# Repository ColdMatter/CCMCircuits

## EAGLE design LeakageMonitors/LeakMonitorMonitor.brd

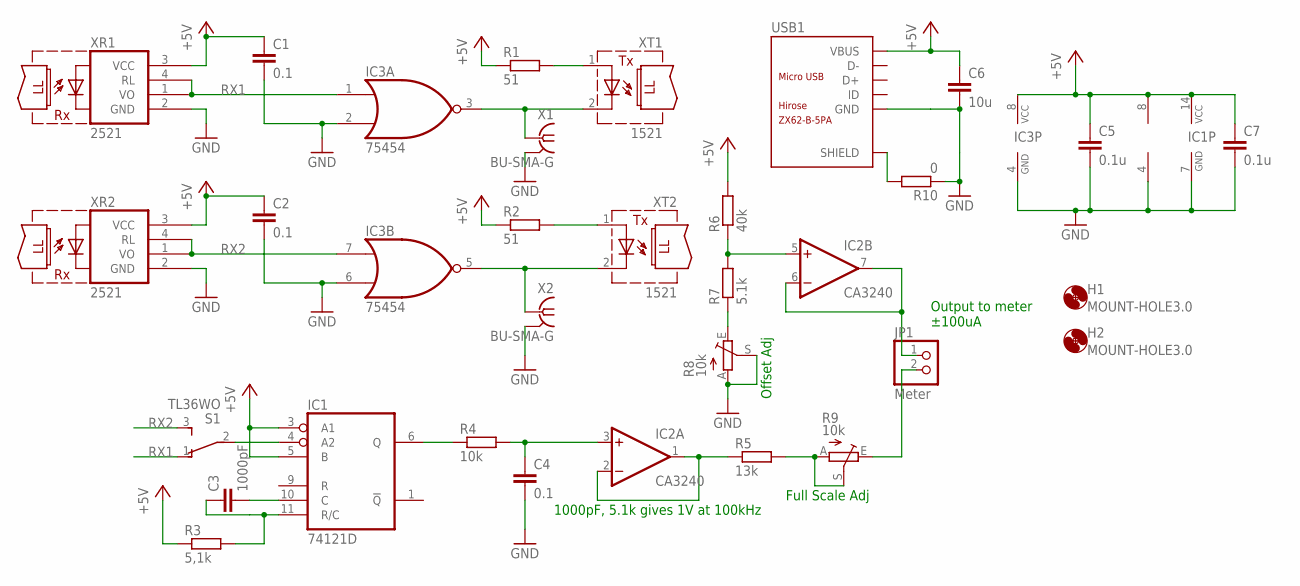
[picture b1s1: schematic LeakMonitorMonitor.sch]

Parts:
C1, C2, C4: 0.1; C0805
C3: 1000pF; C0805
C5, C7: 0.1u; C0805
C6: 10u; C1206
H1, H2: MOUNT-HOLE3.0; 3,0
IC1: 74121D; SO14
IC2: CA3240; SO08
IC3: 75454; D_R-PDSO-G8
JP1: Meter; 1X02
R1, R2: 51; M0805
R3: 5,1k; M0805
R4: 10k; M0805
R5: 13k; M0805
R6: 40k; M0805
R7: 5.1k; M0805
R8, R9: 10k; B25X
R10: 0; R0805
S1: TL36WO; TL3XWO
USB1: ZX62-B-5PA; MICRO-USB5+6P-SMD-0.65-AB
X1, X2: BU-SMA-G
XR1, XR2: 2521; HFBR-15X3
XT1, XT2: 1521; HFBR-15X3

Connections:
+5V: C1.1, C2.1, C5.1, C6.1, C7.1, IC1.3 (A1), IC1.5 (B), IC1.14 (VCC), IC2.8 (V+), IC3.8 (VCC), R1.1, R2.1, R3.1, R6.2, USB1.1 (VBUS), XR1.3 (VCC), XR2.3 (VCC)
GND: C1.2, C2.2, C4.2, C5.2, C6.2, C7.2, IC1.7 (GND), IC2.4 (V-), IC3.2 (I1), IC3.4 (GND), IC3.6 (I1), R8.A, R8.S, R10.1, USB1.5 (GND), X1.2, X1.3 (2), X1.4 (2), X1.5 (2), X2.2, X2.3 (2), X2.4 (2), X2.5 (2), XR1.2 (GND), XR2.2 (GND)
unnamed: IC3.3 (O), X1.1, XT1.2 (C)
unnamed: IC2.5 (+IN), R6.1, R7.2
unnamed: R7.1, R8.E
unnamed: IC3.5 (O), X2.1, XT2.2 (C)
unnamed: R2.2, XT2.1 (A)
unnamed: R1.2, XT1.1 (A)
unnamed: C3.2, IC1.10 (C)
unnamed: IC2.1 (OUT), IC2.2 (-IN), R5.1
unnamed: R5.2, R9.A, R9.S
unnamed: JP1.2, R9.E
unnamed: IC2.6 (-IN), IC2.7 (OUT), JP1.1
unnamed: C3.1, IC1.11 (R/C), R3.2
unnamed: IC1.6 (Q), R4.1
unnamed: C4.1, IC2.3 (+IN), R4.2
unnamed: IC1.4 (A2), S1.2
RX1: IC3.1 (I0), S1.1 (O), XR1.1 (VO), XR1.4 (RL)
RX2: IC3.7 (I0), S1.3 (S), XR2.1 (VO), XR2.4 (RL)
SHIELD: R10.2, USB1.P1 (SHIELD), USB1.P2 (SHIELD), USB1.P3 (SHIELD), USB1.P4 (SHIELD), USB1.P5 (SHIELD), USB1.P6 (SHIELD)

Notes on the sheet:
Output to meter ±100uA
Offset Adj
Full Scale Adj
1000pF, 5.1k gives 1V at 100kHz

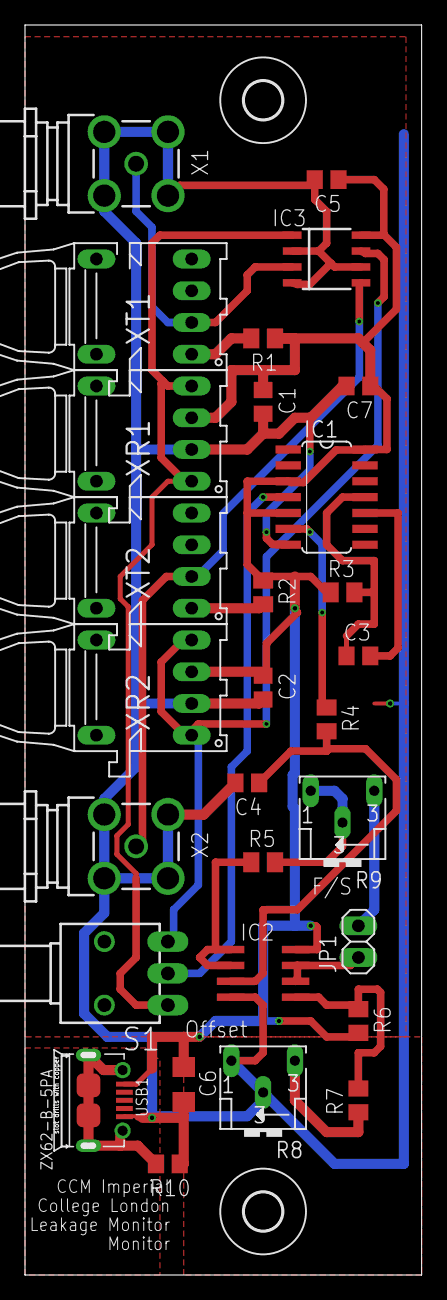
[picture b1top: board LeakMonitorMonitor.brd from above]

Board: 2 copper layers, 31.7 x 100.0 mm, 31 parts (0 on the bottom side), 20 nets.

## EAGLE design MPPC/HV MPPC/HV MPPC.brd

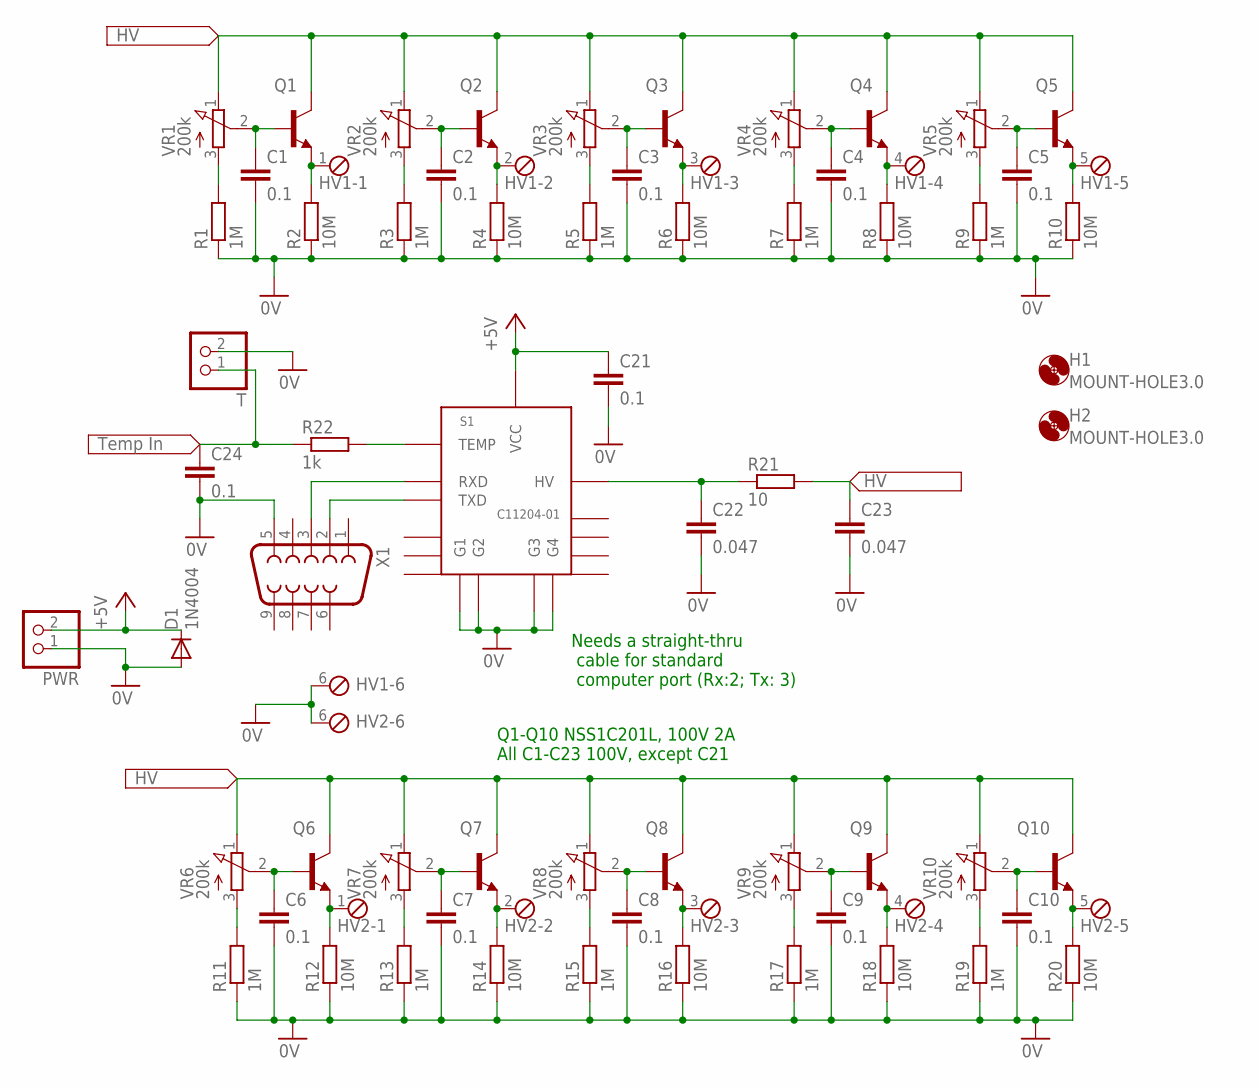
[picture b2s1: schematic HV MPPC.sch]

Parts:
C1, C2, C3, C4, C5, C6, C7, C8, C9, C10, C21, C24: 0.1; C0805
C22, C23: 0.047; C0805
D1: 1N4004; DO41-10
H1, H2: MOUNT-HOLE3.0; 3,0
HV1, HV2: MPT6; 6POL254
PWR: PINHD-1X2; 1X02
Q1, Q2, Q3, Q4, Q5, Q6, Q7, Q8, Q9, Q10: NSS1C201L; SOT23
R1, R3, R5, R7, R9, R11, R13, R15, R17, R19: 1M; R0805
R2, R4, R6, R8, R10, R12, R14, R16, R18, R20: 10M; R0805
R21: 10; R0805
R22: 1k; R0805
S1: C11204-01
T: PINHD-1X2; 1X02
VR1, VR2, VR3, VR4, VR5, VR6, VR7, VR8, VR9, VR10: 200k; 3314G
X1: F09HP

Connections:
0V: C1.2, C2.2, C3.2, C4.2, C5.2, C6.2, C7.2, C8.2, C9.2, C10.2, C21.2, C22.2, C23.2, C24.2, D1.A, HV1.6, HV2.6, PWR.1, R1.1, R2.1, R3.1, R4.1, R5.1, R6.1, R7.1, R8.1, R9.1, R10.1, R11.1, R12.1, R13.1, R14.1, R15.1, R16.1, R17.1, R18.1, R19.1, R20.1, S1.P$2 (G1), S1.P$5 (G2), S1.P$8 (G3), S1.P$15 (G4), T.2, X1.5
+5V: C21.1, D1.C, PWR.2, S1.P$1 (VCC)
HV: C22.1, R21.1, S1.P$10 (HV)
HVOUT: C23.1, Q1.3 (C), Q2.3 (C), Q3.3 (C), Q4.3 (C), Q5.3 (C), Q6.3 (C), Q7.3 (C), Q8.3 (C), Q9.3 (C), Q10.3 (C), R21.2, VR1.1 (E), VR2.1 (E), VR3.1 (E), VR4.1 (E), VR5.1 (E), VR6.1 (E), VR7.1 (E), VR8.1 (E), VR9.1 (E), VR10.1 (E)
unnamed: C1.1, Q1.1 (B), VR1.2 (S)
unnamed: C24.1, R22.1, T.1
unnamed: R22.2, S1.P$16 (TEMP)
unnamed: R1.2, VR1.3 (A)
unnamed: HV1.1, Q1.2 (E), R2.2
unnamed: R3.2, VR2.3 (A)
unnamed: HV1.2, Q2.2 (E), R4.2
unnamed: R5.2, VR3.3 (A)
unnamed: HV1.3, Q3.2 (E), R6.2
unnamed: R7.2, VR4.3 (A)
unnamed: HV1.4, Q4.2 (E), R8.2
unnamed: R9.2, VR5.3 (A)
unnamed: HV1.5, Q5.2 (E), R10.2
unnamed: C2.1, Q2.1 (B), VR2.2 (S)
unnamed: C3.1, Q3.1 (B), VR3.2 (S)
unnamed: C4.1, Q4.1 (B), VR4.2 (S)
unnamed: C5.1, Q5.1 (B), VR5.2 (S)
unnamed: C6.1, Q6.1 (B), VR6.2 (S)
unnamed: C7.1, Q7.1 (B), VR7.2 (S)
unnamed: C8.1, Q8.1 (B), VR8.2 (S)
unnamed: C9.1, Q9.1 (B), VR9.2 (S)
unnamed: C10.1, Q10.1 (B), VR10.2 (S)
unnamed: R11.2, VR6.3 (A)
unnamed: HV2.1, Q6.2 (E), R12.2
unnamed: R13.2, VR7.3 (A)
unnamed: HV2.2, Q7.2 (E), R14.2
unnamed: R15.2, VR8.3 (A)
unnamed: HV2.3, Q8.2 (E), R16.2
unnamed: R17.2, VR9.3 (A)
unnamed: R19.2, VR10.3 (A)
unnamed: HV2.5, Q10.2 (E), R20.2
unnamed: HV2.4, Q9.2 (E), R18.2
RX: S1.P$3 (RXD), X1.3
TX: S1.P$4 (TXD), X1.2

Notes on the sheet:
Q1-Q10 NSS1C201L, 100V 2A All C1-C23 100V, except C21
Needs a straight-thru cable for standard computer port (Rx:2; Tx: 3)

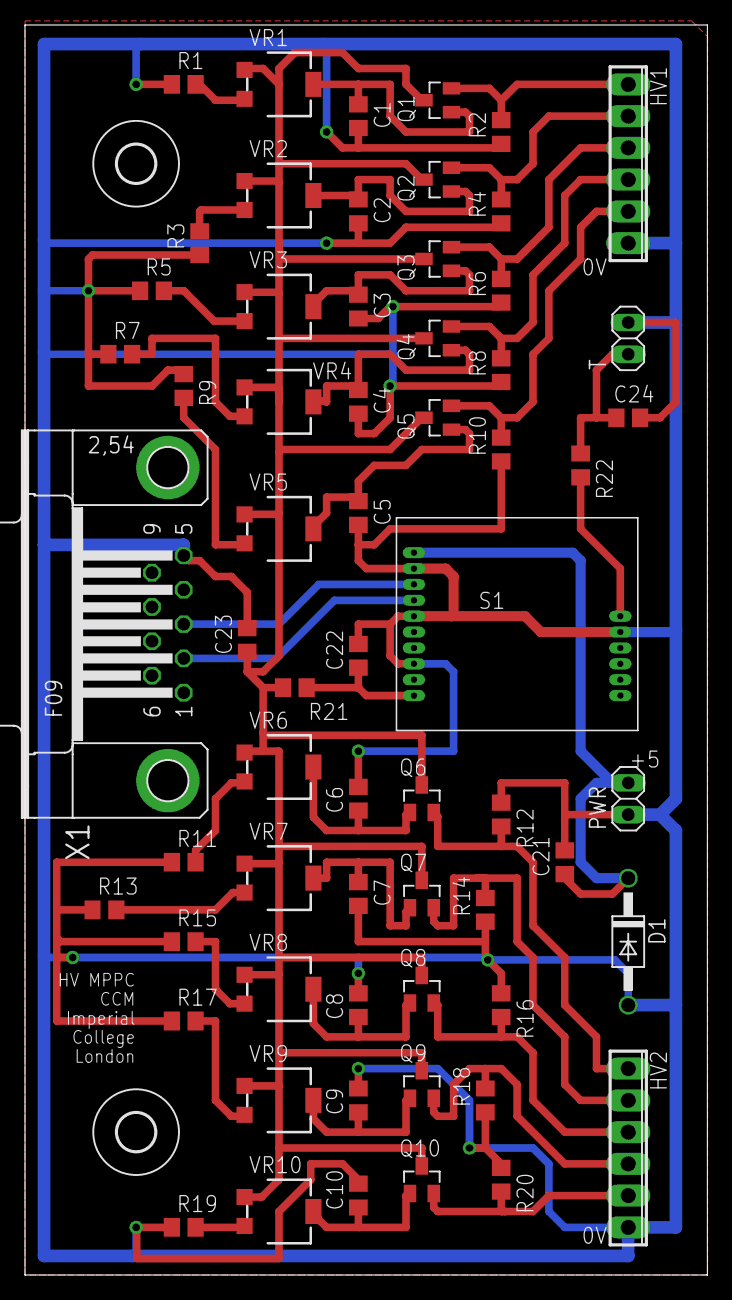
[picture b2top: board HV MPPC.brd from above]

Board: 2 copper layers, 54.6 x 100.0 mm, 65 parts (0 on the bottom side), 38 nets.

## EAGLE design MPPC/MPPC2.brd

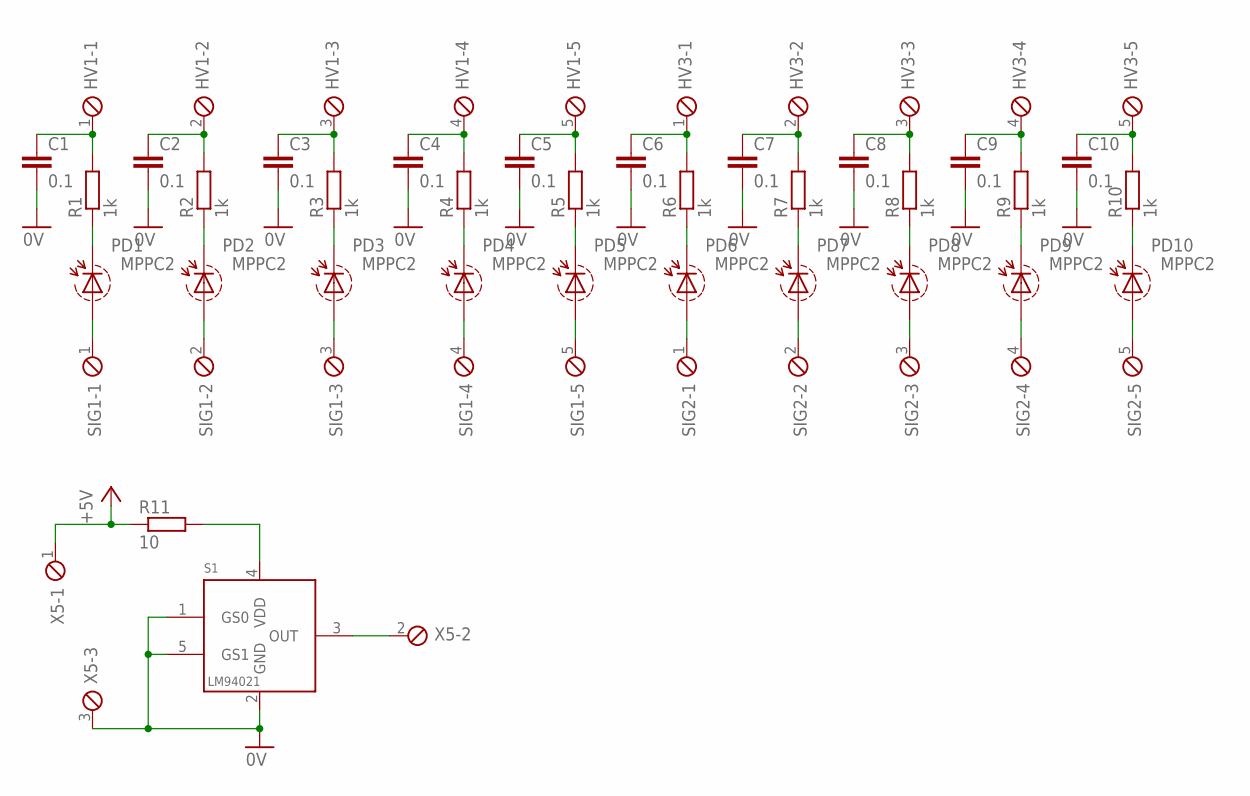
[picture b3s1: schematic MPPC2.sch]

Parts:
C1, C2, C3, C4, C5, C6, C7, C8, C9, C10: 0.1; C0805K
HV1, HV3: MPT5; 5POL254
PD1, PD2, PD3, PD4, PD5, PD6, PD7, PD8, PD9, PD10: MPPC2; S13360-6050VE
R1, R2, R3, R4, R5, R6, R7, R8, R9, R10: 1k; M0805
R11: 10; R0805
S1: LM94021; DCK_R-PDSO-G5
SIG1, SIG2: MPT5; 5POL254
X5: MPT3; 3POL254

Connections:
0V: C1.2, C2.2, C3.2, C4.2, C5.2, C6.2, C7.2, C8.2, C9.2, C10.2, S1.1 (GS0), S1.2 (GND), S1.5 (GS1), X5.3
+5V: R11.1, X5.1
unnamed: PD2.C1 (CATH), PD2.C2 (CATH), PD2.C3 (CATH), PD2.C4 (CATH), R2.1
unnamed: R11.2, S1.4 (VDD)
unnamed: S1.3 (OUT), X5.2
unnamed: C1.1, HV1.1, R1.2
unnamed: PD1.C1 (CATH), PD1.C2 (CATH), PD1.C3 (CATH), PD1.C4 (CATH), R1.1
unnamed: PD1.A1 (ANODE), PD1.A2 (ANODE), PD1.A3 (ANODE), PD1.A4 (ANODE), SIG1.1
unnamed: PD2.A1 (ANODE), PD2.A2 (ANODE), PD2.A3 (ANODE), PD2.A4 (ANODE), SIG1.2
unnamed: PD3.A1 (ANODE), PD3.A2 (ANODE), PD3.A3 (ANODE), PD3.A4 (ANODE), SIG1.3
unnamed: PD4.A1 (ANODE), PD4.A2 (ANODE), PD4.A3 (ANODE), PD4.A4 (ANODE), SIG1.4
unnamed: PD5.A1 (ANODE), PD5.A2 (ANODE), PD5.A3 (ANODE), PD5.A4 (ANODE), SIG1.5
unnamed: PD6.A1 (ANODE), PD6.A2 (ANODE), PD6.A3 (ANODE), PD6.A4 (ANODE), SIG2.1
unnamed: PD7.A1 (ANODE), PD7.A2 (ANODE), PD7.A3 (ANODE), PD7.A4 (ANODE), SIG2.2
unnamed: PD8.A1 (ANODE), PD8.A2 (ANODE), PD8.A3 (ANODE), PD8.A4 (ANODE), SIG2.3
unnamed: PD9.A1 (ANODE), PD9.A2 (ANODE), PD9.A3 (ANODE), PD9.A4 (ANODE), SIG2.4
unnamed: PD10.A1 (ANODE), PD10.A2 (ANODE), PD10.A3 (ANODE), PD10.A4 (ANODE), SIG2.5
unnamed: C2.1, HV1.2, R2.2
unnamed: C3.1, HV1.3, R3.2
unnamed: C4.1, HV1.4, R4.2
unnamed: C5.1, HV1.5, R5.2
unnamed: C6.1, HV3.1, R6.2
unnamed: C7.1, HV3.2, R7.2
unnamed: C8.1, HV3.3, R8.2
unnamed: C9.1, HV3.4, R9.2
unnamed: C10.1, HV3.5, R10.2
unnamed: PD3.C1 (CATH), PD3.C2 (CATH), PD3.C3 (CATH), PD3.C4 (CATH), R3.1
unnamed: PD4.C1 (CATH), PD4.C2 (CATH), PD4.C3 (CATH), PD4.C4 (CATH), R4.1
unnamed: PD5.C1 (CATH), PD5.C2 (CATH), PD5.C3 (CATH), PD5.C4 (CATH), R5.1
unnamed: PD6.C1 (CATH), PD6.C2 (CATH), PD6.C3 (CATH), PD6.C4 (CATH), R6.1
unnamed: PD7.C1 (CATH), PD7.C2 (CATH), PD7.C3 (CATH), PD7.C4 (CATH), R7.1
unnamed: PD8.C1 (CATH), PD8.C2 (CATH), PD8.C3 (CATH), PD8.C4 (CATH), R8.1
unnamed: PD9.C1 (CATH), PD9.C2 (CATH), PD9.C3 (CATH), PD9.C4 (CATH), R9.1
unnamed: PD10.C1 (CATH), PD10.C2 (CATH), PD10.C3 (CATH), PD10.C4 (CATH), R10.1

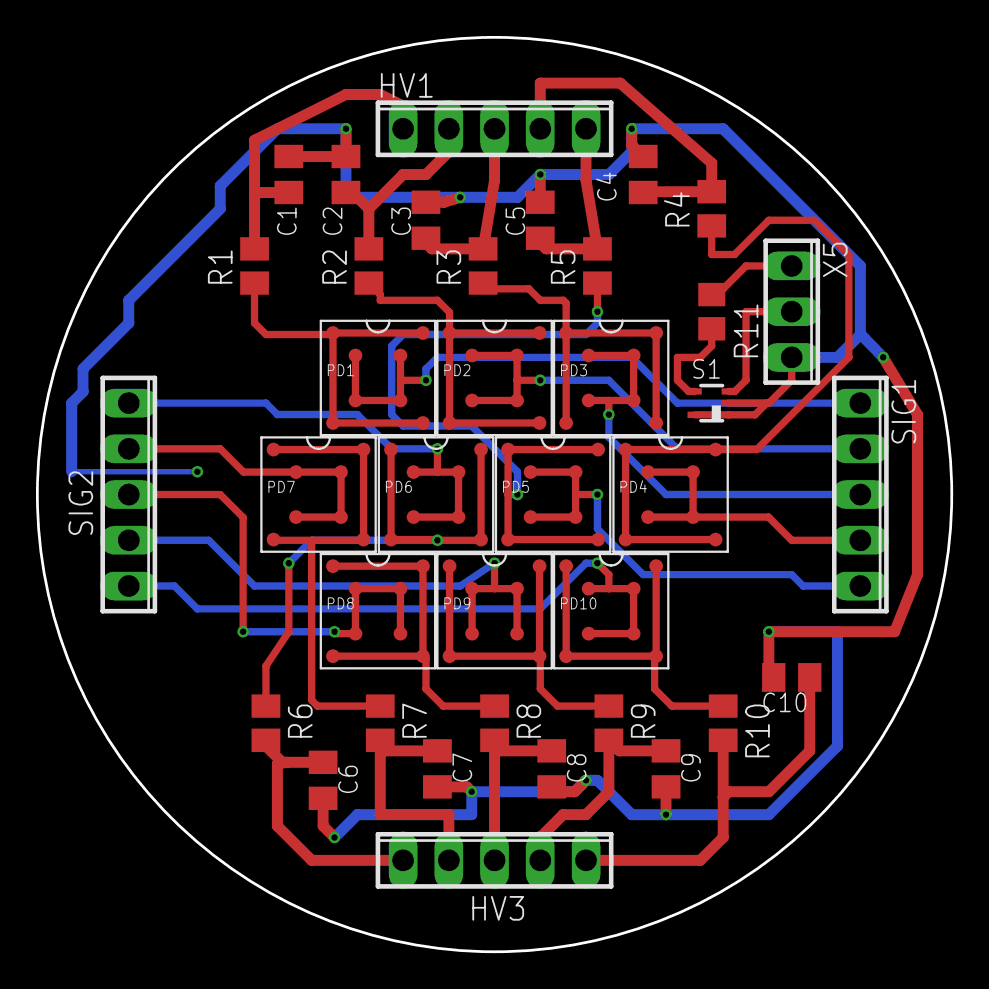
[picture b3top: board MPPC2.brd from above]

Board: 2 copper layers, 50.8 x 50.8 mm, 37 parts (0 on the bottom side), 34 nets.

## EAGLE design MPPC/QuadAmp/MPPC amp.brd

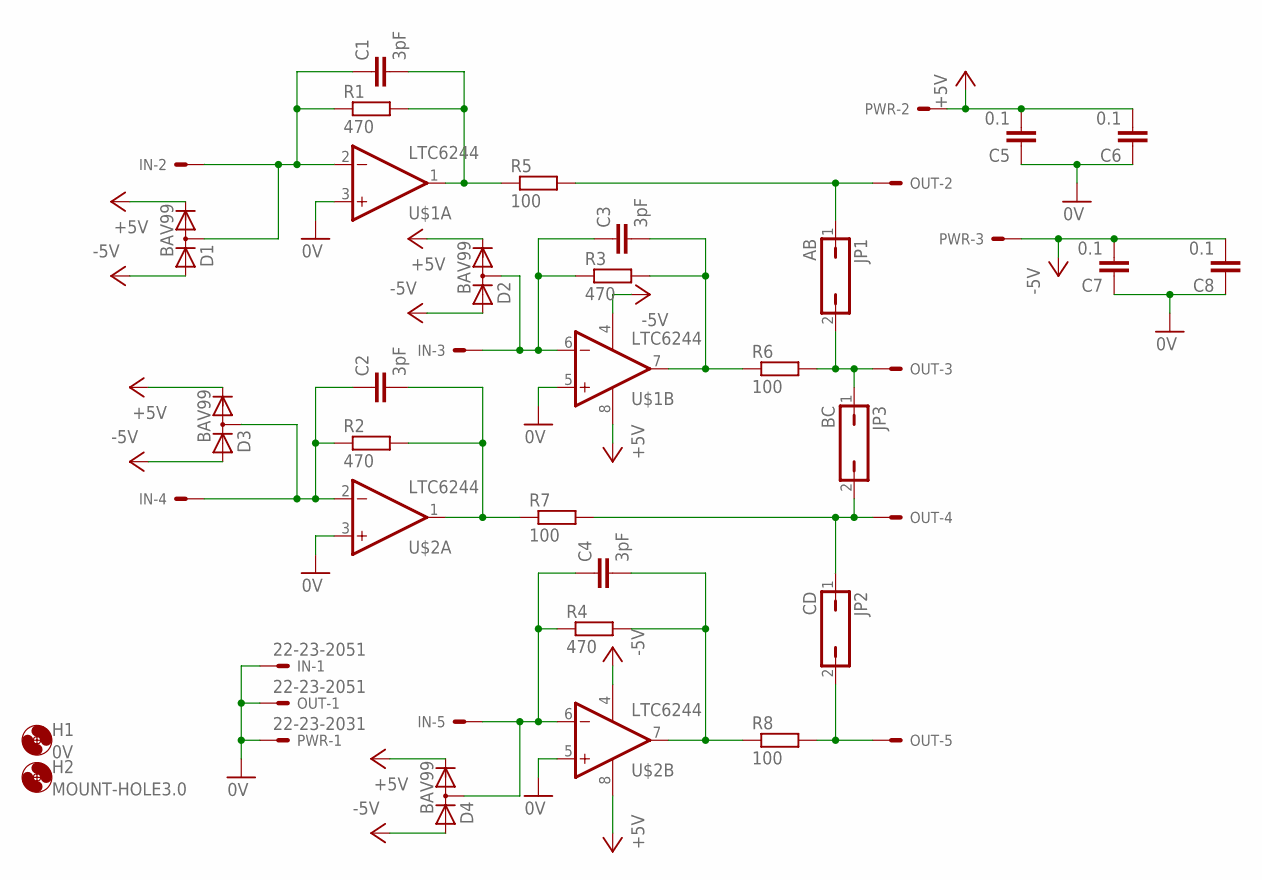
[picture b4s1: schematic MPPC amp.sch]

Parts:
C1, C2, C3, C4: 3pF; C0805
C5, C6, C7, C8: 0.1; C0805
D1, D2, D3, D4: BAV99; SOT23
H1: 0V; 3,0
H2: MOUNT-HOLE3.0; 3,0
IN: 22-23-2051
JP1: AB; JP1
JP2: CD; JP1
JP3: BC; JP1
OUT: 22-23-2051
PWR: 22-23-2031
R1, R2, R3, R4: 470; R0805
R5, R6, R7, R8: 100; R0805
U$1, U$2: LTC6244; MSOP08

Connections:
0V: C5.1, C6.1, C7.1, C8.1, IN.1, OUT.1, PWR.1, U$1.3 (+IN), U$1.5 (+IN), U$2.3 (+IN), U$2.5 (+IN)
+5V: C5.2, C6.2, D1.2 (C), D2.2 (C), D3.2 (C), D4.2 (C), PWR.2, U$1.8 (V+), U$2.8 (V+)
-5V: C7.2, C8.2, D1.1 (A), D2.1 (A), D3.1 (A), D4.1 (A), PWR.3, U$1.4 (V-), U$2.4 (V-)
unnamed: C4.1, D4.3 (AC), IN.5, R4.1, U$2.6 (-IN)
unnamed: C2.1, D3.3 (AC), IN.4, R2.1, U$2.2 (-IN)
unnamed: C3.1, D2.3 (AC), IN.3, R3.1, U$1.6 (-IN)
unnamed: C1.1, D1.3 (AC), IN.2, R1.1, U$1.2 (-IN)
unnamed: C1.2, R1.2, R5.1, U$1.1 (OUT)
unnamed: C2.2, R2.2, R7.1, U$2.1 (OUT)
unnamed: C3.2, R3.2, R6.1, U$1.7 (OUT)
unnamed: C4.2, R4.2, R8.1, U$2.7 (OUT)
unnamed: JP1.2, JP3.1, OUT.3, R6.2
unnamed: JP1.1, OUT.2, R5.2
unnamed: JP2.1, JP3.2, OUT.4, R7.2
unnamed: JP2.2, OUT.5, R8.2

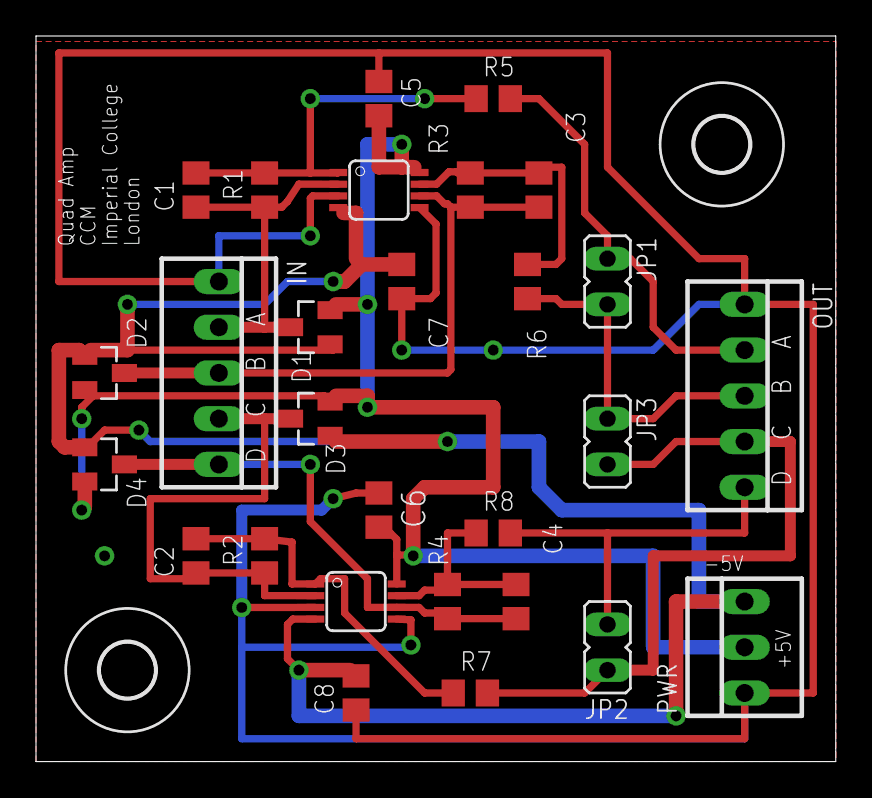
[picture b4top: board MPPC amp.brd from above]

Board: 2 copper layers, 44.4 x 40.3 mm, 30 parts (0 on the bottom side), 15 nets.
